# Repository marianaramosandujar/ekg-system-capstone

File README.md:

EKG System Setup Instructions (Windows)
These instructions are for setting up and running the EKG system on Windows.
OPTION ONE:

Window/Linux users:
Download Python here before starting: https://www.python.org/downloads/release/python-3133/

1. Click the code button above and click download zip.
2. In your file explore it, extract the entire folder.
3. Open the folder the folder named ekg_system_capstone, and find the file called
    **setup_and_run.bat**
4. Double click that file and it should start up.

Mac Users: 
Download Python here before starting: https://www.python.org/downloads/release/python-3133/
1. Click the Code button above and click Download ZIP.
2. In Finder, locate the downloaded ZIP file and extract the entire folder.
3. Open the extracted folder named ekg_system_capstone.
4. Find the file called **setup_and_run_mac.sh.**
5. Right click the file and select Open With then Terminal (or open Terminal and navigate to the folder).
6. In terminal, run this once to allow execution
**chmod +x setup_and_run_mac.sh**
7. then type this in your terminal window
**./setup_and_run_mac.sh**
then application will start up.

OPTION 2 TO DOWNLOAD IF MORE FAMILIAR WITH GIT:
Make sure your device has Python and Git already installed, if not, follow these instructions. 
 Download the latest version of Python in this link https://www.python.org/downloads/
 Download the latest version of Git https://git-scm.com/install/

1. Clone the repository in the terminal window of your device, type this.

**git clone https://github.com/marianaramosandujar/ekg-system-capstone.git**

2. Move into this folder, in your terminal type this
 
  **cd ekg-system-capstone**

3. Create and activate virtual environment, in your terminal type this.

If windows or Linux, type this

**python -m venv venv venv\Scripts\activate**

If Mac, type this
**python3 -m venv venv venv\Scripts\activate** 

4. Install dependencies by typing this into your terminal.

Windows - **pip install -r requirements.txt** 

Mac- **pip3 install -r requirements.txt**

5. Run the UI
For Windows - **python ui_main.py**

For Mac - **python3 ui_main.py**

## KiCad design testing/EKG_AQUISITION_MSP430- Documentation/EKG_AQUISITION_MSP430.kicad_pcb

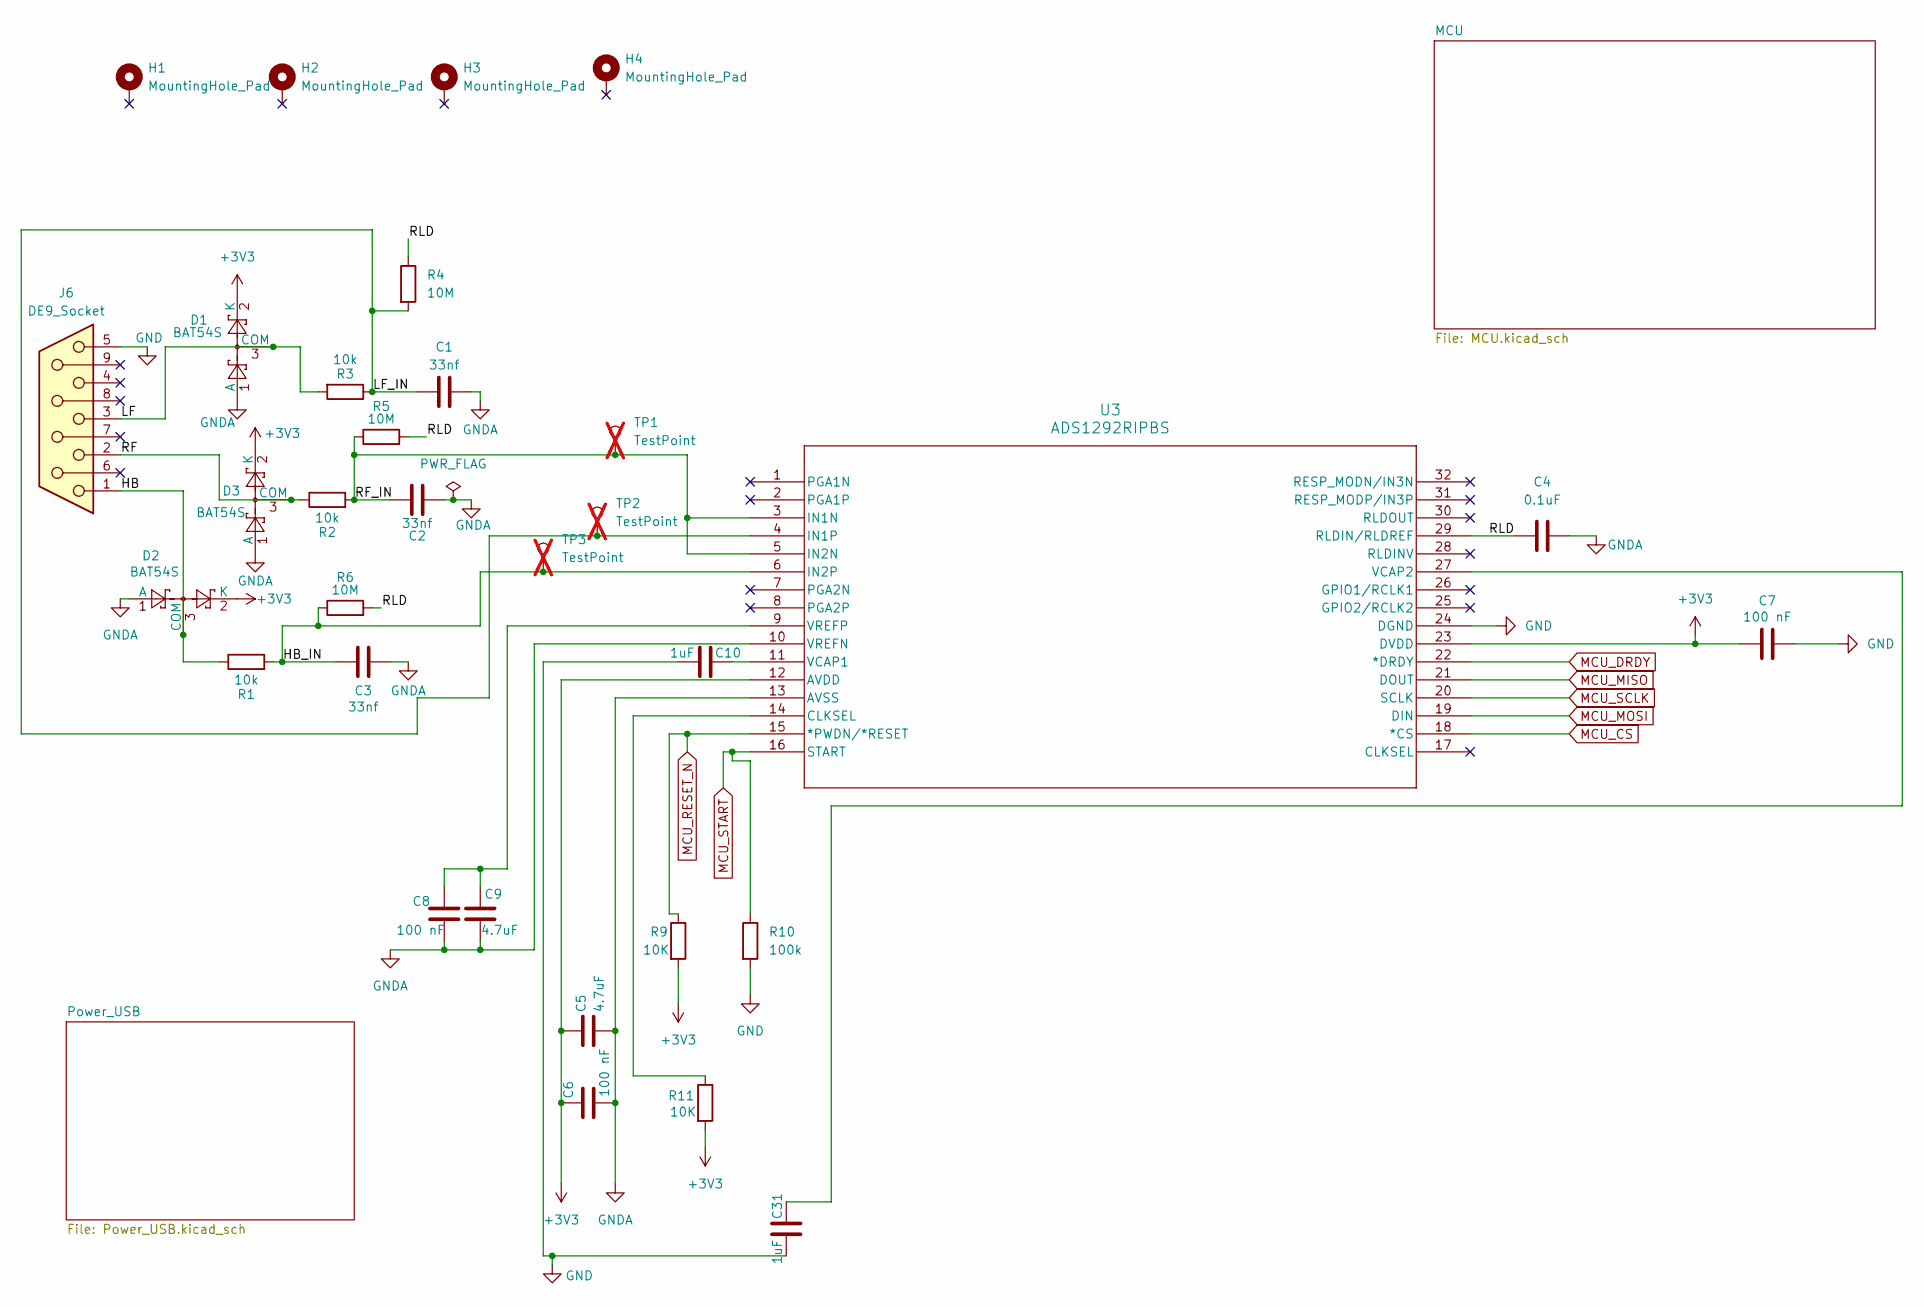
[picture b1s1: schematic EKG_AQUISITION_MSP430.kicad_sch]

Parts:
C1, C2, C3: 33nf; C_0603_1608Metric
C4: 0.1uF; C_0603_1608Metric
C5, C9: 4.7uF; C_0805_2012Metric
C6, C7, C8: 100 nF; C_0603_1608Metric
C10, C31: 1uF; C_0603_1608Metric
D1, D2, D3: BAT54S; SOT-23
H1, H2, H3, H4: MountingHole_Pad; MountingHole_3.2mm_M3
J6: DE9_Socket; DSUB-9_Socket_Horizontal_P2.77x2.84mm_EdgePinOffset4.94mm_H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
R1, R2, R3: 10k; R_0603_1608Metric
R4, R5, R6: 10M; R_0603_1608Metric
R9, R11: 10K; R_0603_1608Metric
R10: 100k; R_0603_1608Metric
TP1, TP2, TP3: TestPoint; TestPoint_Pad_D2.0mm; not fitted
U3: ADS1292RIPBS

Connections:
+3V3: C5.1, C6.1, C7.1, D1.2 (K), D2.2 (K), D3.2 (K), R9.2, R11.2, U3.12 (AVDD), U3.23 (DVDD); also elsewhere on the board
/HB: D2.3 (COM), J6.1, R1.1
/HB_IN: C3.1, R1.2, R6.1, TP3.1, U3.6 (IN2P)
/LF: D1.3 (COM), J6.3, R3.2
/LF_IN: C1.1, R3.1, R4.2, TP2.1, U3.4 (IN1P)
/RF: D3.3 (COM), J6.2, R2.1
/RF_IN: C2.2, R2.2, R5.1, TP1.1, U3.3 (IN1N), U3.5 (IN2N)
/RLD: C4.1, R4.1, R5.2, R6.2, U3.29 (RLDIN/RLDREF)
GND: C7.2, C10.2, C31.2, J6.5, R10.2, U3.24 (DGND); also elsewhere on the board
GNDA: C1.2, C2.1, C3.2, C4.2, C5.2, C6.2, C8.1, C9.2, D1.1 (A), D2.1 (A), D3.1 (A), U3.10 (VREFN), U3.13 (AVSS)
MCU_CS: U3.18 (*CS); also elsewhere on the board
MCU_DRDY: U3.22 (*DRDY); also elsewhere on the board
MCU_MISO: U3.21 (DOUT); also elsewhere on the board
MCU_MOSI: U3.19 (DIN); also elsewhere on the board
MCU_RESET_N: R9.1, U3.15 (*PWDN/*RESET); also elsewhere on the board
MCU_SCLK: U3.20 (SCLK); also elsewhere on the board
MCU_START: R10.1, U3.16 (START); also elsewhere on the board
unnamed: R11.1, U3.14 (CLKSEL)
unnamed: C10.1, U3.11 (VCAP1)
unnamed: C31.1, U3.27 (VCAP2)
unnamed: C8.2, C9.1, U3.9 (VREFP)

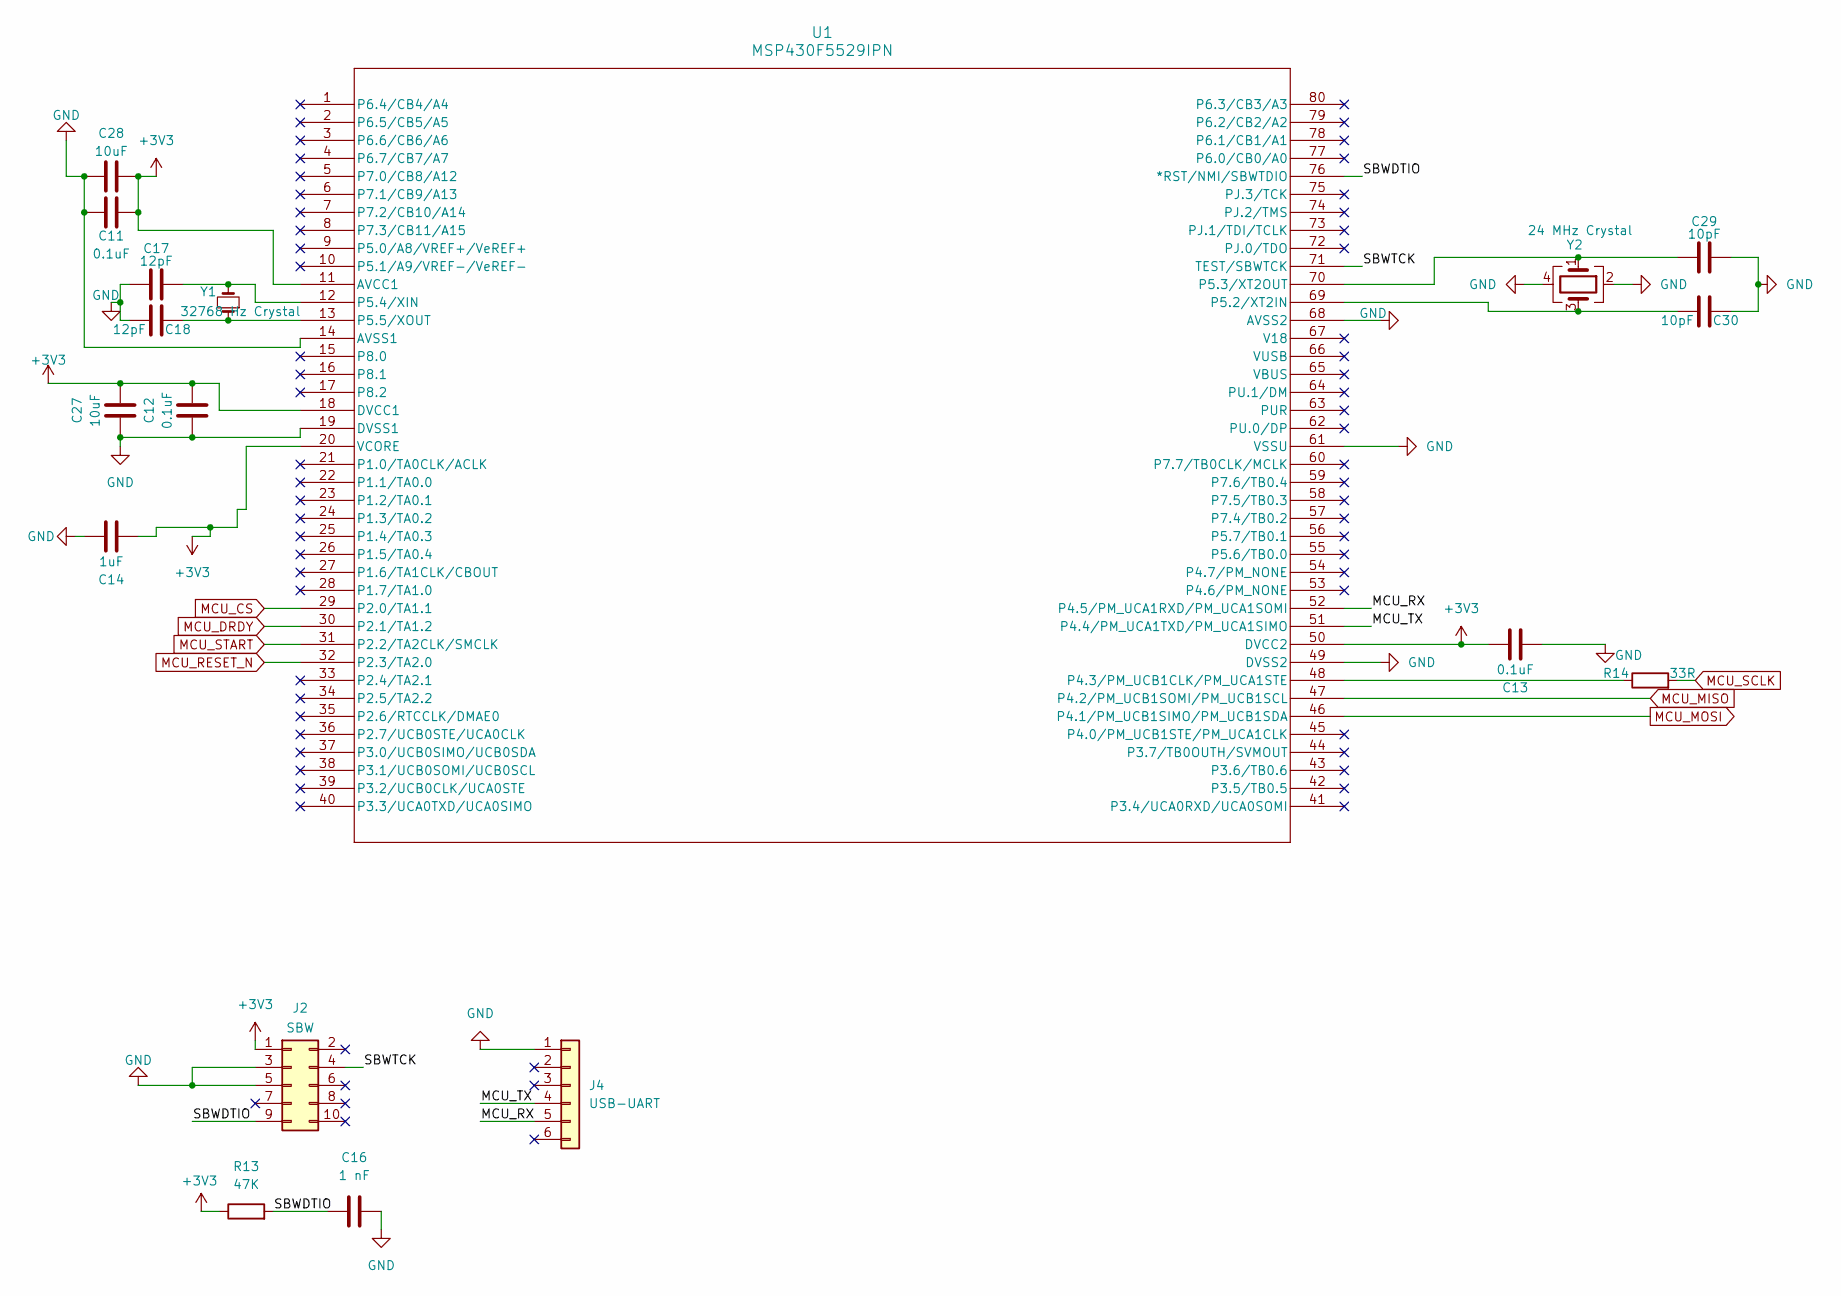
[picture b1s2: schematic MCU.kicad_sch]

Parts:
C11, C12, C13: 0.1uF; C_0603_1608Metric
C14: 1uF; C_0603_1608Metric
C16: 1 nF; C_0603_1608Metric
C17, C18: 12pF; C_0603_1608Metric
C27: 10uF; C_0805_2012Metric
C28: 10uF; C_0603_1608Metric
C29, C30: 10pF; C_0603_1608Metric
J2: SBW; PinHeader_2x05_P2.54mm_Vertical
J4: USB-UART; PinHeader_1x06_P2.54mm_Vertical
R13: 47K; R_0603_1608Metric
R14: 33R; R_0603_1608Metric
U1: MSP430F5529IPN
Y1: 32768 Hz Crystal; Custom 2 pin crystal
Y2: 24 MHz Crystal; Custom Crystal 24MHZ

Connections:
+3V3: C11.2, C12.2, C13.2, C14.1, C27.2, C28.2, J2.1, R13.1, U1.11 (AVCC1), U1.18 (DVCC1), U1.20 (VCORE), U1.50 (DVCC2); also elsewhere on the board
/MCU/MCU_RX: J4.5, U1.52 (P4.5/PM_UCA1RXD/PM_UCA1SOMI)
/MCU/MCU_TX: J4.4, U1.51 (P4.4/PM_UCA1TXD/PM_UCA1SIMO)
/MCU/SBWDTIO: C16.2, J2.9, R13.2, U1.76 (*RST/NMI/SBWTDIO)
/MCU/SBWTCK: J2.4, U1.71 (TEST/SBWTCK)
GND: C11.1, C12.1, C13.1, C14.2, C16.1, C17.1, C18.1, C27.1, C28.1, C29.2, C30.2, J2.3, J2.5, J4.1, U1.14 (AVSS1), U1.19 (DVSS1), U1.49 (DVSS2), U1.61 (VSSU), U1.68 (AVSS2), Y2.2, Y2.4; also elsewhere on the board
MCU_CS: U1.29 (P2.0/TA1.1); also elsewhere on the board
MCU_DRDY: U1.30 (P2.1/TA1.2); also elsewhere on the board
MCU_MISO: U1.47 (P4.2/PM_UCB1SOMI/PM_UCB1SCL); also elsewhere on the board
MCU_MOSI: U1.46 (P4.1/PM_UCB1SIMO/PM_UCB1SDA); also elsewhere on the board
MCU_RESET_N: U1.32 (P2.3/TA2.0); also elsewhere on the board
MCU_SCLK: R14.2; also elsewhere on the board
MCU_START: U1.31 (P2.2/TA2CLK/SMCLK); also elsewhere on the board
unnamed: R14.1, U1.48 (P4.3/PM_UCB1CLK/PM_UCA1STE)
unnamed: C30.1, U1.69 (P5.2/XT2IN), Y2.3
unnamed: C29.1, U1.70 (P5.3/XT2OUT), Y2.1
unnamed: C17.2, U1.12 (P5.4/XIN), Y1.2
unnamed: C18.2, U1.13 (P5.5/XOUT), Y1.1

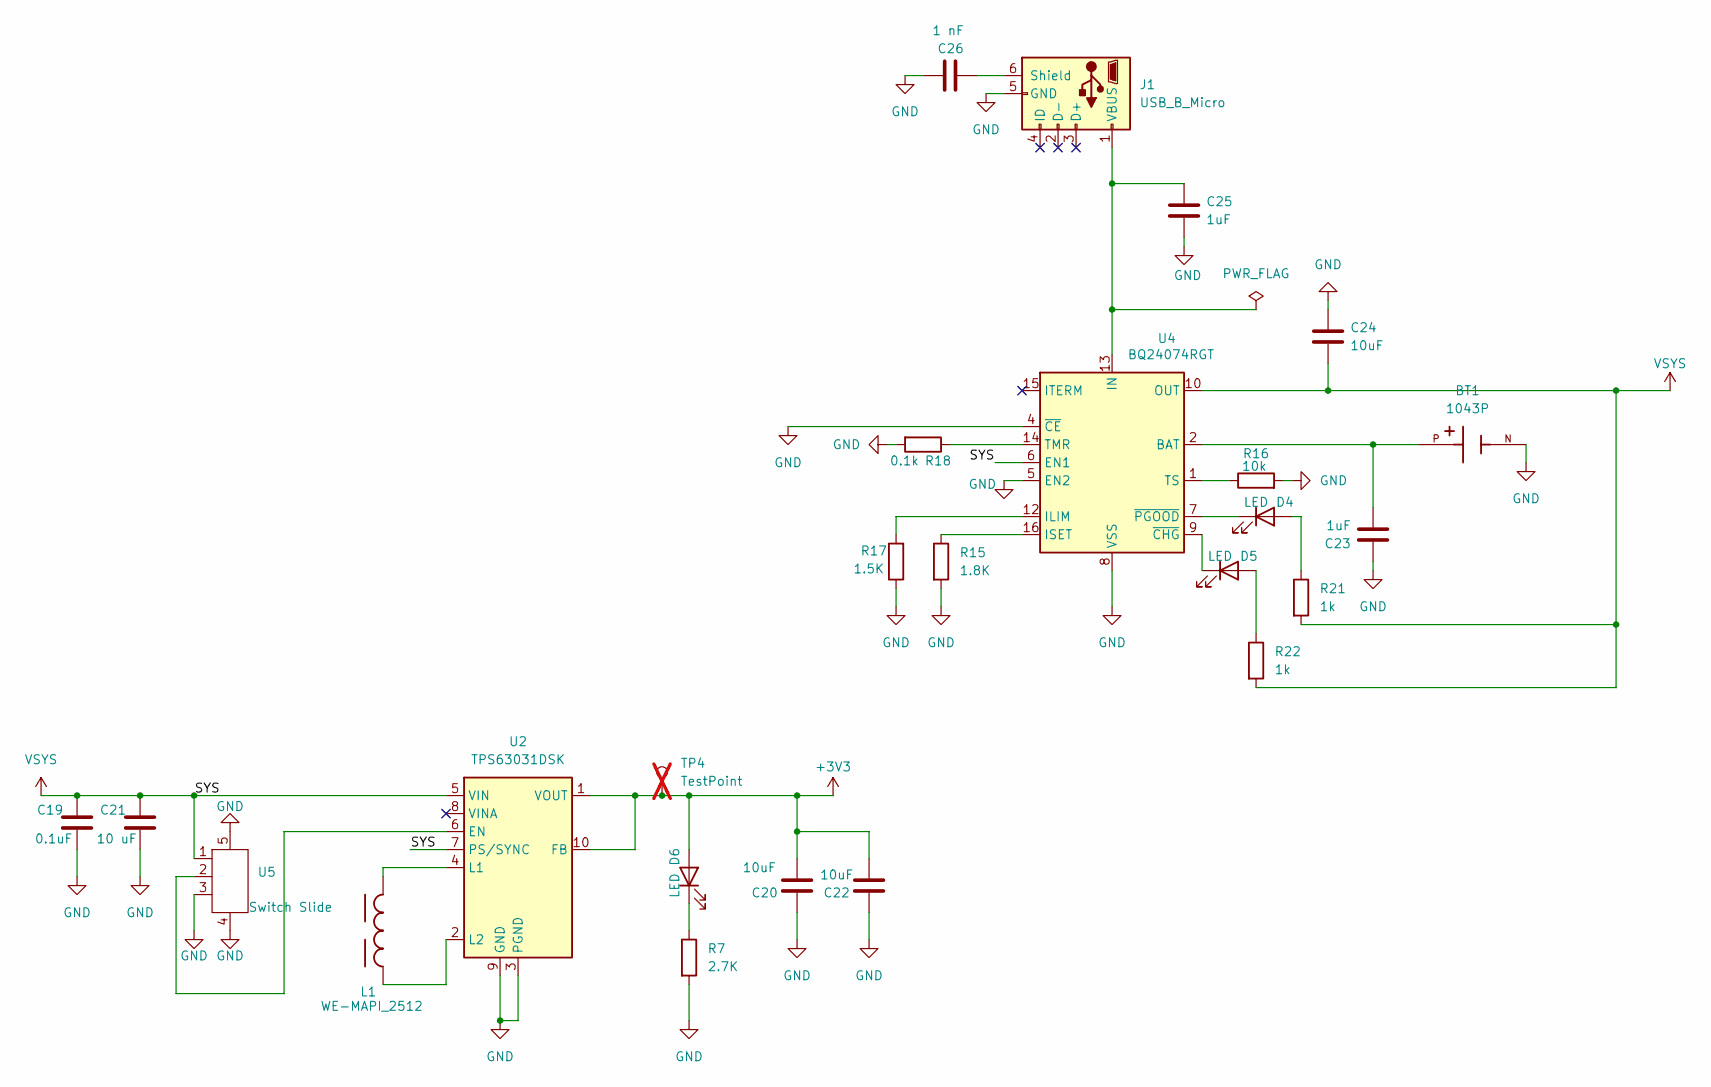
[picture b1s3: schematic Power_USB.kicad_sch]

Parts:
BT1: 1043P; BAT_1043P; PARTREV D
C19: 0.1uF; C_0603_1608Metric
C20, C22, C24: 10uF; C_0805_2012Metric
C21: 10 uF; C_0805_2012Metric
C23, C25: 1uF; C_0603_1608Metric
C26: 1 nF; C_0603_1608Metric
D4, D5, D6: LED; LED_0805_2012Metric
J1: USB_B_Micro; USB_Micro-AB_Molex_47590-0001
L1: WE-MAPI_2512
R7: 2.7K; R_0603_1608Metric
R15: 1.8K; R_0603_1608Metric
R16: 10k; R_0603_1608Metric
R17: 1.5K; R_0603_1608Metric
R18: 0.1k; R_0603_1608Metric
R21, R22: 1k; R_0603_1608Metric
TP4: TestPoint; TestPoint_Pad_D2.0mm; not fitted
U2: TPS63031DSK; WSON-10-1EP_2.5x2.5mm_P0.5mm_EP1.2x2mm
U4: BQ24074RGT; VQFN-16-1EP_3x3mm_P0.5mm_EP1.6x1.6mm
U5: Switch Slide; Custom switch 1

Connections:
+3V3: C20.2, C22.2, D6.2 (A), TP4.1, U2.1 (VOUT), U2.10 (FB); also elsewhere on the board
GND: BT1.N, C19.1, C20.1, C21.1, C22.1, C23.1, C24.1, C25.2, C26.1, J1.5 (GND), R7.2, R15.2, R16.2, R17.1, R18.2, U2.3 (PGND), U2.9 (GND), U2.11 (PGND), U4.4 (~CE), U4.5 (EN2), U4.8 (VSS), U4.17 (VSS), U5.3, U5.4, U5.5; also elsewhere on the board
unnamed: BT1.P, C23.2, U4.2 (BAT), U4.3 (BAT)
unnamed: D4.2 (A), R21.1
unnamed: D4.1 (K), U4.7 (~PGOOD)
unnamed: D5.2 (A), R22.1
unnamed: D5.1 (K), U4.9 (~CHG)
unnamed: D6.1 (K), R7.1
unnamed: C26.2, J1.6 (Shield)
unnamed: C25.1, J1.1 (VBUS), U4.13 (IN)
unnamed: U2.6 (EN), U5.2
unnamed: L1.2, U2.4 (L1)
unnamed: L1.1, U2.2 (L2)
unnamed: R17.2, U4.12 (ILIM)
unnamed: R15.1, U4.16 (ISET)
unnamed: R18.1, U4.14 (TMR)
unnamed: R16.1, U4.1 (TS)
VSYS: C19.2, C21.2, C24.2, R21.2, R22.2, U2.5 (VIN), U2.7 (PS/SYNC), U4.6 (EN1), U4.10 (OUT), U4.11 (OUT), U5.1

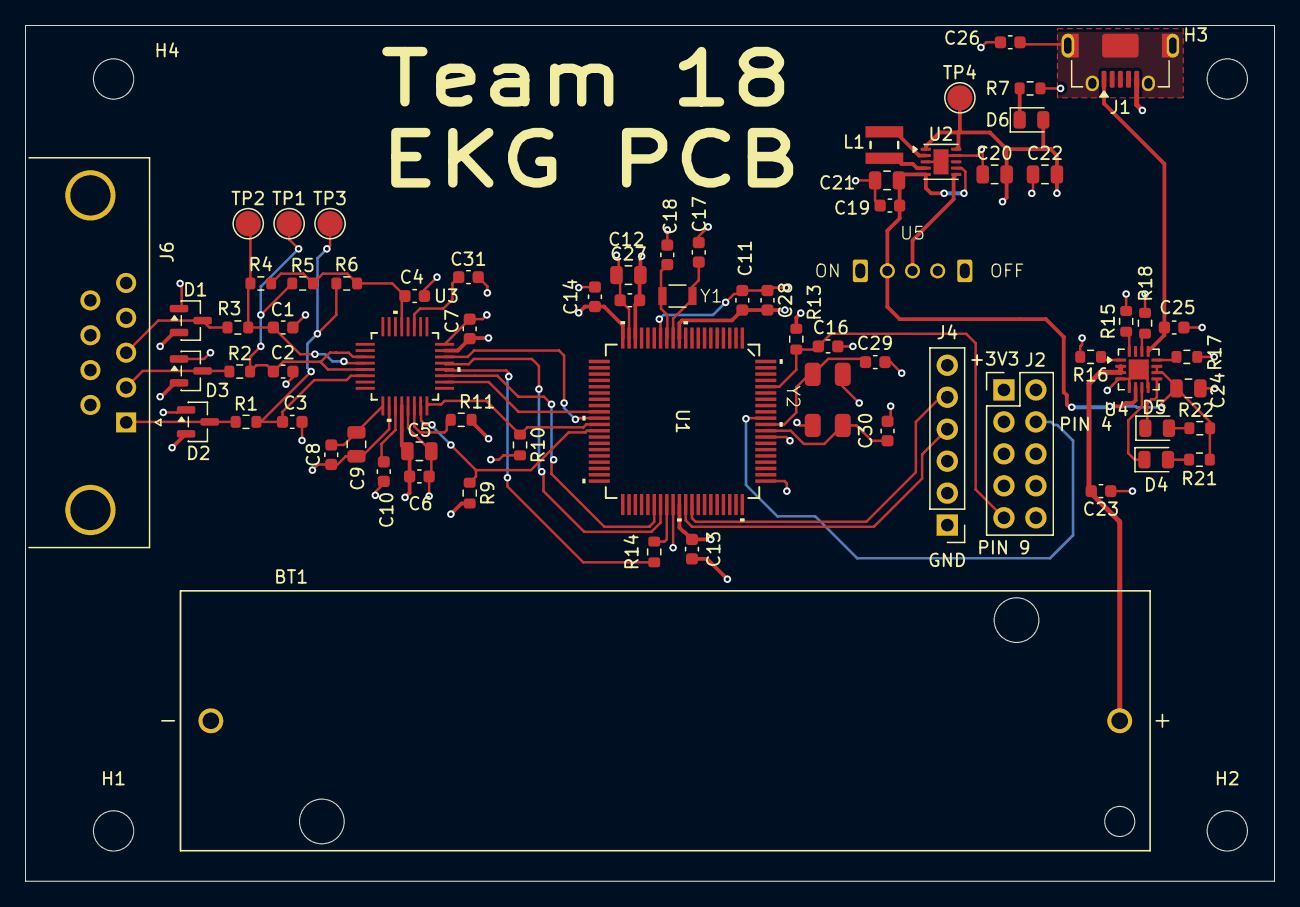
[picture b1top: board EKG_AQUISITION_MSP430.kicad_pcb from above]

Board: 4 copper layers, 99.2 x 68.0 mm, 75 parts (0 on the bottom side), 46 nets.

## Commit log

2025-11-04 Initial plan
2025-11-04 Implement complete EKG data processing application
2025-11-04 Add LICENSE and CONTRIBUTING documentation
2025-11-04 Add QUICKSTART guide for new users
2025-11-04 Security fix: Update scipy to version 1.8.0 to address vulnerability
2025-11-04 New changes to the UI that adds the clinical view as well as a new example file.
2025-11-06 new changes to ui for clinicla and analyze view. works for csv now
2025-11-06 fixing my git commit that broke for some reason
2025-11-07 Fix ekg_system folder (remove submodule issue)
2025-11-07 Fix folder duplication (flatten ekg_system directory)
2025-11-07 Remove duplicate example files and finalize folder cleanup
2025-11-07 fix duplicate files
2025-11-07 Add lab_data folder and CSV files (override gitignore)
2025-11-07 Update .gitignore to allow lab_data CSV files
2025-11-07 pls work
2025-11-07 Flatten structure (remove space and fix ekg_files folder)
2025-11-07 final changes
2025-11-13 save local edits before rebase
2025-11-17 Removed unused files, and added new live view
2025-11-20 Update README with project directory navigation
    Added a step to navigate into the project directory before activating the virtual environment.
2025-11-20 Added new requirements to run on lab computers
2025-11-20 Updated read me with new download details
2025-12-02 changed analyze window to be similar colors to clinical view
2026-01-29 changes to test microcontroller
2026-02-03 new changes
2026-02-03 new read me for sydney
2026-02-26 move work from main to branch
2026-02-26 new changes for mpc
2026-02-26 pushing this change for board
2026-02-26 new more chANGES SINCE CANT SEE UI
2026-02-26 ok try tis
2026-02-26 trying
2026-02-26 make it red
2026-03-03 sydneys file of th elogger
2026-03-03 testing folder
2026-03-03 new changes for the msp
2026-03-03 updated code
2026-03-05 new changes for saving csv file
2026-03-05 fixing zoom
2026-03-05 fixing time error?
2026-03-10 changes to try and fix the 5 seconds craziness
2026-03-10 new changes for possible demo and changing this code to main branch
2026-03-10 read me changes
2026-03-10 old changes
2026-03-10 possible working fix
2026-03-10 changes to icon ui to match all the same boxes
2026-03-11 ppossible final ui changes for demo
2026-03-11 changes to open the live view first
2026-03-11 changes to not have start button change until msp is detected
2026-03-11 saves csv data to a file called live data
2026-03-11 testing
2026-03-11 changes to make the button smaller in clinical
2026-03-31 new millivolt conversion
2026-03-31 changes to mv?
2026-04-07 Update branch name in README instructions
2026-04-07 Revise EKG system setup instructions
    Updated setup instructions for clarity and added Python and Git download links.
2026-04-07 Update README steps for cloning and setup
2026-04-07 Fix virtual environment activation instructions
    Corrected instructions for activating the virtual environment and updated the step numbers accordingly.
2026-04-07 Revise README for clearer setup instructions
    Updated instructions for cloning the repository, activating the virtual environment, and running the UI for clarity and consistency.
2026-04-07 Revise EKG system setup instructions in README
    Updated setup instructions for clarity and consistency.
2026-04-07 Revise README instructions for virtual environment setup
    Updated instructions for creating and activating a virtual environment and adjusted the numbering of steps.
2026-04-07 setup scripts
2026-04-08 update to requiremenrs for download
2026-04-08 testing new changes
2026-04-08 view
2026-04-08 na back
2026-04-08 requirements text change
2026-04-08 requirements change
2026-04-08 changes to the axis
2026-04-08 files that include Rahuls PCB board documents
2026-04-08 changes to mv
2026-04-10 changes for mv
2026-04-10 new changes for doing r-peak tests
2026-04-10 Enhance EKG system setup instructions
    Added setup instructions for Mac users and clarified steps for Windows users.
